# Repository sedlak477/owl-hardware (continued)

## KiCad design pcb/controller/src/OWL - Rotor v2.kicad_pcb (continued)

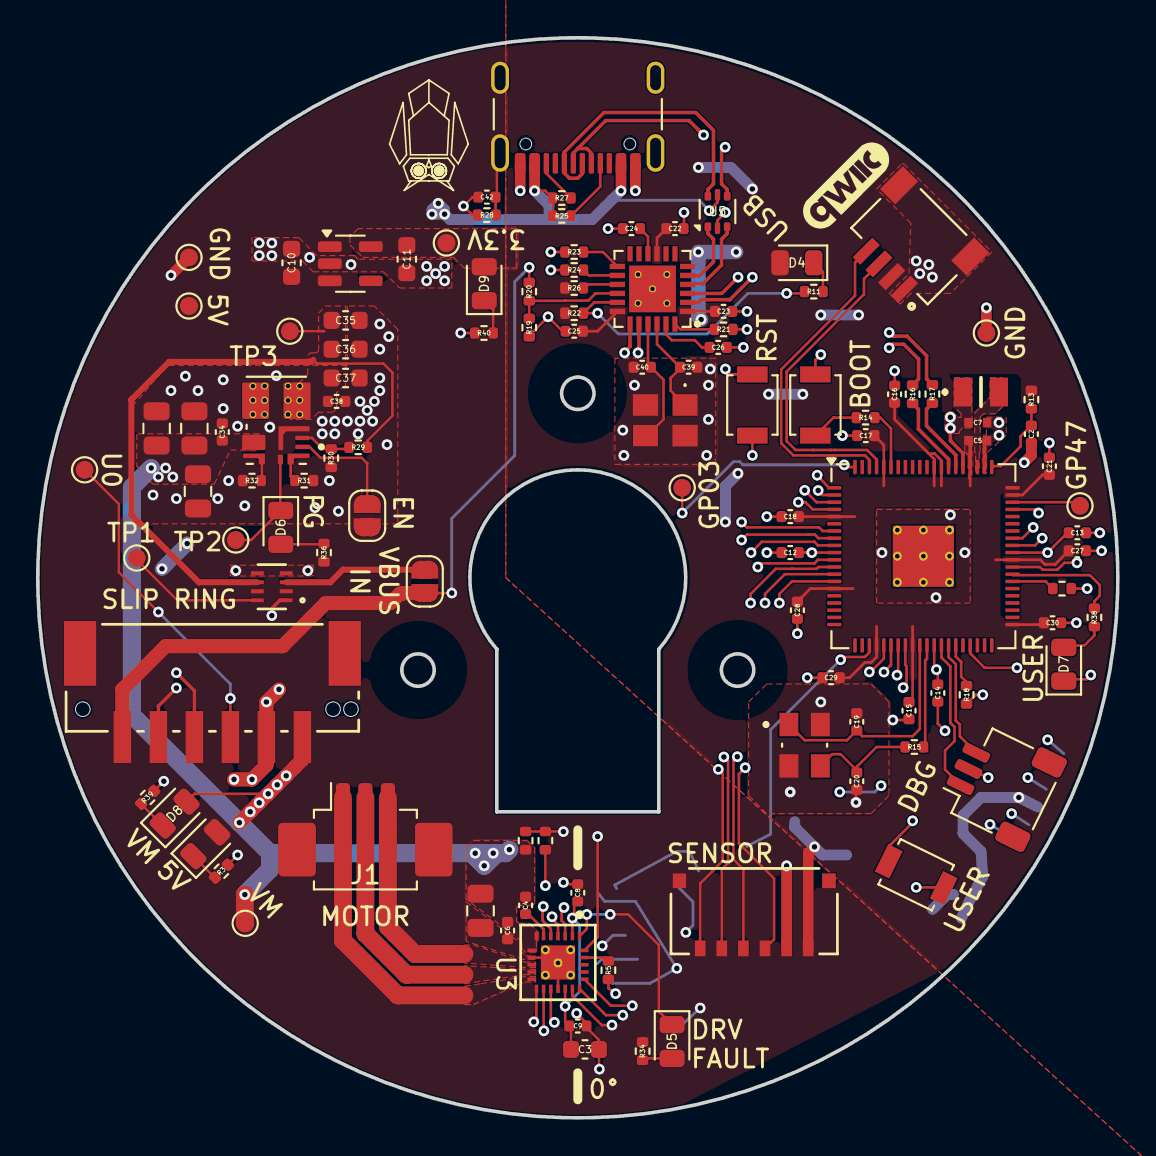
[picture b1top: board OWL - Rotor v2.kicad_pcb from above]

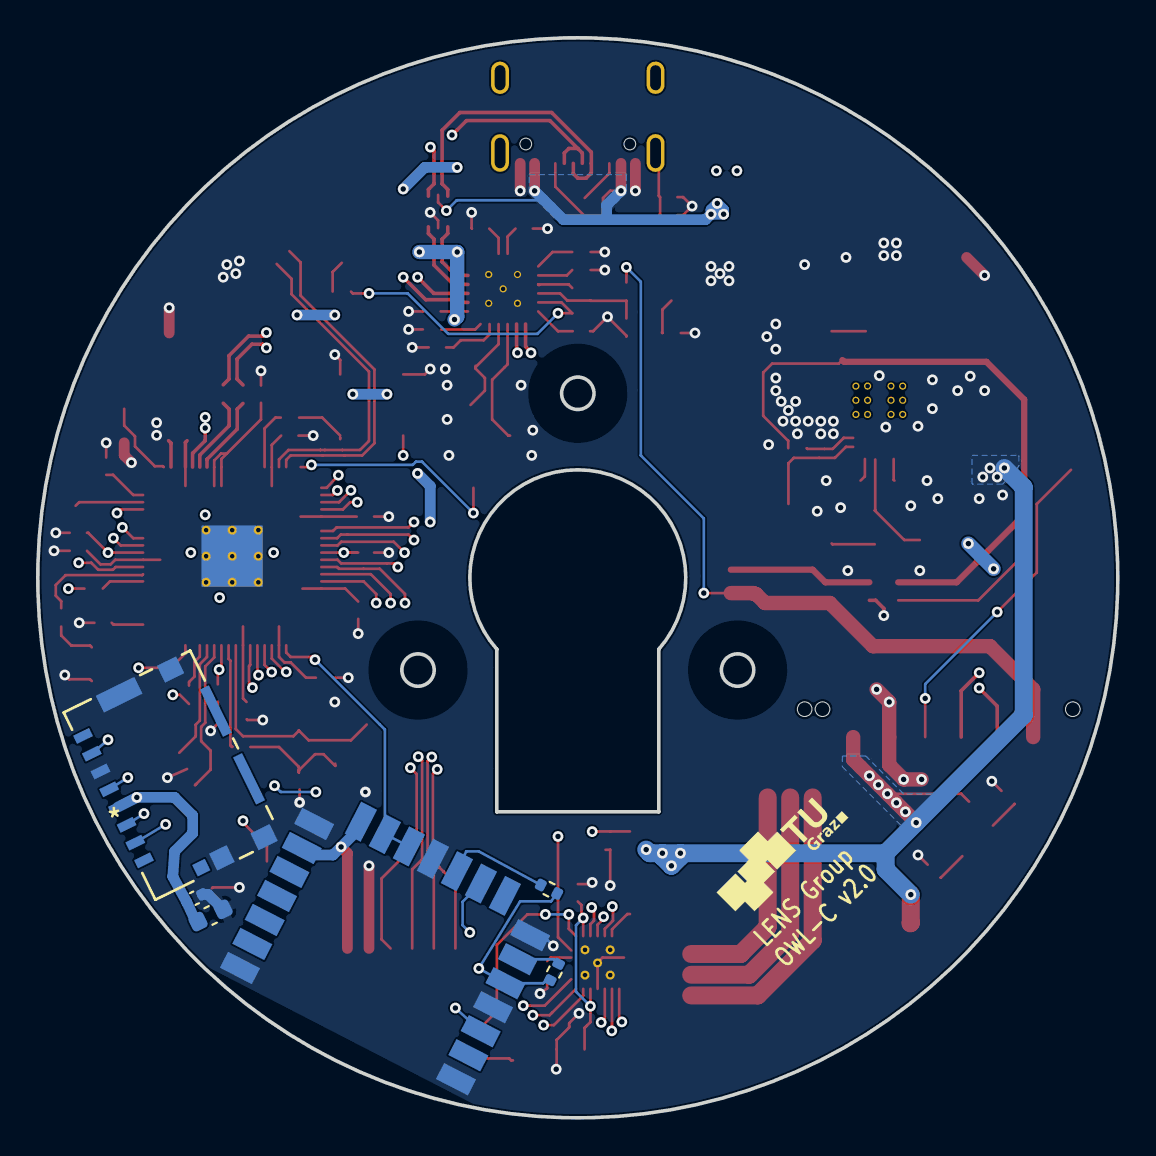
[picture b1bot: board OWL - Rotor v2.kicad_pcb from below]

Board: 4 copper layers, 60.0 x 60.0 mm, 117 parts (6 on the bottom side), 93 nets.

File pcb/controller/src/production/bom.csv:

Designator,Footprint,Quantity,Value,LCSC Part #
C1,0805,1,10u 50V,C28241
"C10, C11, C3, C44",0603,4,10u,
"C12, C13, C15, C16, C17, C18, C21, C23, C25, C26, C27, C28, C29, C30, C38, C43, C8, C9",0402,18,100n,
"C14, C2, C5, C7",0402,4,4.7u,
"C19, C20",0402,2,15p,
"C22, C24",0402,2,1u,
"C31, C32, C33",0805,3,10u 50V,
"C34, C4, C6",0402,3,100n 50V,
"C35, C36, C37",0603,3,22u,
"C39, C40",0402,2,18p,
C42,0402,1,100n 250V,
"D2, D8, D9",0805,3,KT-0805G,
D4,0805,1,KT-0805Y,
"D5, D6",0805,2,KT-0805R,
D7,0805,1,XL-1608UBC-04,
IC1,QFN50P400X400X100-25N,1,USB2422-I_MJ,
J1,Molex_PicoBlade_53261-0371_1x03-1MP_P1.25mm_Horizontal,1,Motor,
J3,USB_C_Receptacle_GCT_USB4105-xx-A_16P_TopMnt_Horizontal,1,USB_C_Receptacle_USB2.0_14P,
J4,CONN_BM06B-PASS-1_JST,1,Slip Ring,
J5,CONN06_781715006_MOL,1,781715006,
J6,JST_SH_SM03B-SRSS-TB_1x03-1MP_P1.00mm_Horizontal,1,SM03B-SRSS-TB,
J8,105162-0001_MOL,1,Micro_SD_Card,C3177046
J9,JST_SM04B-SRSS-TB_LF__SN_,1,SM04B-SRSS-TB_LF__SN_,C160404
L1,AOTAB201610S3R3101T,1,3.3u,
PS1,CONV_TPSM84338RCJR,1,TPSM84338RCJR,
R1,0402,1,470,
R11,0402,1,270,
R13,0402,1,33,
"R14, R15, R18, R34, R36, R41",0402,6,1k,
"R16, R17",0402,2,27,
"R19, R20",0402,2,100k,
"R2, R4",0402,2,10k,
R21,0402,1,12k,
"R22, R23, R24, R26, R5",0402,5,47k,
"R25, R27",0402,2,22k,
R28,0402,1,330,
R29,0402,1,110k,
R3,0402,1,510,
R30,0402,1,15k,
R31,0402,1,0,
R32,0402,1,18k,
R38,0402,1,360,
R39,0402,1,4.7k,
R40,0402,1,150,
R6,0402,1,1.43k,
SW1,SW_SPST_B3U-1000P,1,BOOTSEL,
SW2,SW_SPST_B3U-1000P,1,RESET,
SW3,SW_SPST_B3U-1000P,1,USER,
TP1,TestPoint_Pad_D1.0mm,1,STATUS,
TP10,TestPoint_Pad_D1.0mm,1,GP03,
"TP12, TP7",TestPoint_Pad_D1.0mm,2,GND,
TP2,TestPoint_Pad_D1.0mm,1,REG PG,
TP3,TestPoint_Pad_D1.0mm,1,REG 5V,
TP4,TestPoint_Pad_D1.0mm,1,3.3V,
TP5,TestPoint_Pad_D1.0mm,1,GP47,
TP6,TestPoint_Pad_D1.0mm,1,5V,
TP8,TestPoint_Pad_D1.0mm,1,U0,
TP9,TestPoint_Pad_D1.0mm,1,VMotor,
U1,SOT-23-5,1,AP2112K-3.3,C23380830
U2,SOT-5X3_DRL_TEX,1,LM66200DRLR,
U3,RRW0024-MFG,1,PDRV8311HRRWR,
U4,QFN-80-1EP_10x10mm_P0.4mm_EP3.4x3.4mm_ThermalVias,1,RP2354B,
U5,SOT-666,1,USBLC6-2P6,
U6,rpi_rmc20452t,1,<value>,
Y1,XTAL_ABM8-272-T3,1,ABM8-272-T3,
Y2,7M24000MAAJT,1,7M-24.000MAAJ-T,

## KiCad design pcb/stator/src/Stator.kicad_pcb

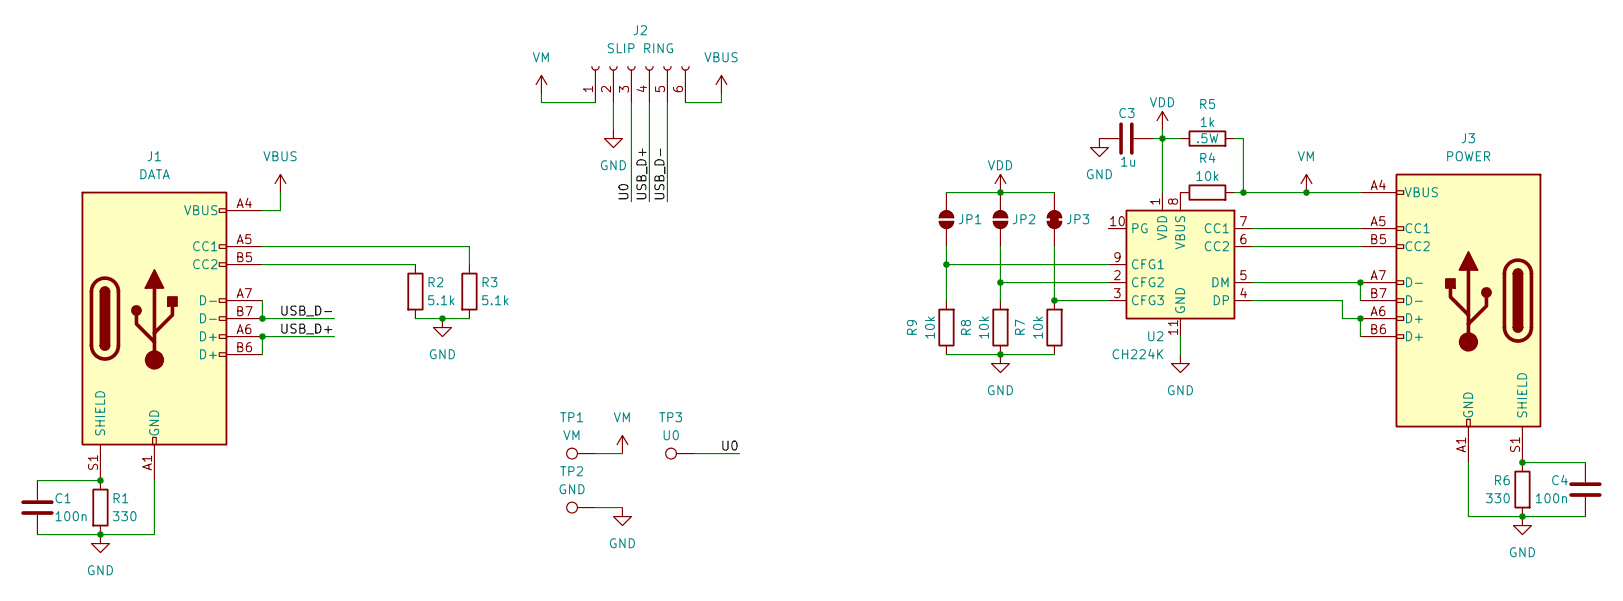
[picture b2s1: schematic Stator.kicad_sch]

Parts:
C1, C4: 100n; C_0402_1005Metric; MPN 0402F104M500NT; LCSC C1581
C3: 1u; C_0402_1005Metric; MPN CL05A105KA5NQNC; LCSC C52923
J1: DATA; USB_C_Receptacle_GCT_USB4110; MPN USB4110-GF-A; LCSC C5143397
J2: SLIP RING; CONN_BM06B-PASS-1_JST; MPN BM06B-PASS-TFT(LF)(SN); LCSC C265376
J3: POWER; USB_C_Receptacle_GCT_USB4110; MPN USB4110-GF-A; LCSC C5143397
JP1: C1; SolderJumper-2_P1.3mm_Open_RoundedPad1.0x1.5mm
JP2: C2; SolderJumper-2_P1.3mm_Open_RoundedPad1.0x1.5mm
JP3: C3; SolderJumper-2_P1.3mm_Bridged_RoundedPad1.0x1.5mm
R1, R6: 330; R_0402_1005Metric; MPN 0402WGF3300TCE; LCSC C25104
R2, R3: 5.1k; R_0402_1005Metric; MPN 0402WGF5101TCE; LCSC C25905
R4, R7, R8, R9: 10k; R_0402_1005Metric; MPN 0402WGF1002TCE; LCSC C25744
R5: 1k; R_0805_2012Metric; MPN AS05W2J0102T5E; LCSC C560481
TP1: VM; TestPoint_Pad_2.0x2.0mm
TP2: GND; TestPoint_Pad_2.0x2.0mm
TP3: U0; TestPoint_Pad_2.0x2.0mm
U2: CH224K; SSOP-10-1EP_3.9x4.9mm_P1mm_EP2.1x3.3mm; MPN CH224K; LCSC C970725

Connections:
/U0: J2.3, TP3.1
/USB_D+: J1.A6 (D+), J1.B6 (D+), J2.4
/USB_D-: J1.A7 (D-), J1.B7 (D-), J2.5
GND: C1.2, C3.2, C4.2, J1.A1 (GND), J1.A12 (GND), J1.B1 (GND), J1.B12 (GND), J2.2, J3.A1 (GND), J3.A12 (GND), J3.B1 (GND), J3.B12 (GND), R1.2, R2.2, R3.2, R6.2, R7.1, R8.1, R9.1, TP2.1, U2.11 (GND)
unnamed: J1.A5 (CC1), R3.1
unnamed: J1.B5 (CC2), R2.1
unnamed: C1.1, J1.S1 (SHIELD), R1.1
unnamed: J3.A5 (CC1), U2.7 (CC1)
unnamed: J3.B5 (CC2), U2.6 (CC2)
unnamed: C4.1, J3.S1 (SHIELD), R6.1
unnamed: JP1.1 (A), R9.2, U2.9 (CFG1)
unnamed: JP2.1 (A), R8.2, U2.2 (CFG2)
unnamed: JP3.1 (A), R7.2, U2.3 (CFG3)
unnamed: J3.A7 (D-), J3.B7 (D-), U2.5 (DM)
unnamed: J3.A6 (D+), J3.B6 (D+), U2.4 (DP)
unnamed: R4.1, U2.8 (VBUS)
VBUS: J1.A4 (VBUS), J1.A9 (VBUS), J1.B4 (VBUS), J1.B9 (VBUS), J2.6
VDD: C3.1, JP1.2 (B), JP2.2 (B), JP3.2 (B), R5.1, U2.1 (VDD)
VM: J2.1, J3.A4 (VBUS), J3.A9 (VBUS), J3.B4 (VBUS), J3.B9 (VBUS), R4.2, R5.2, TP1.1

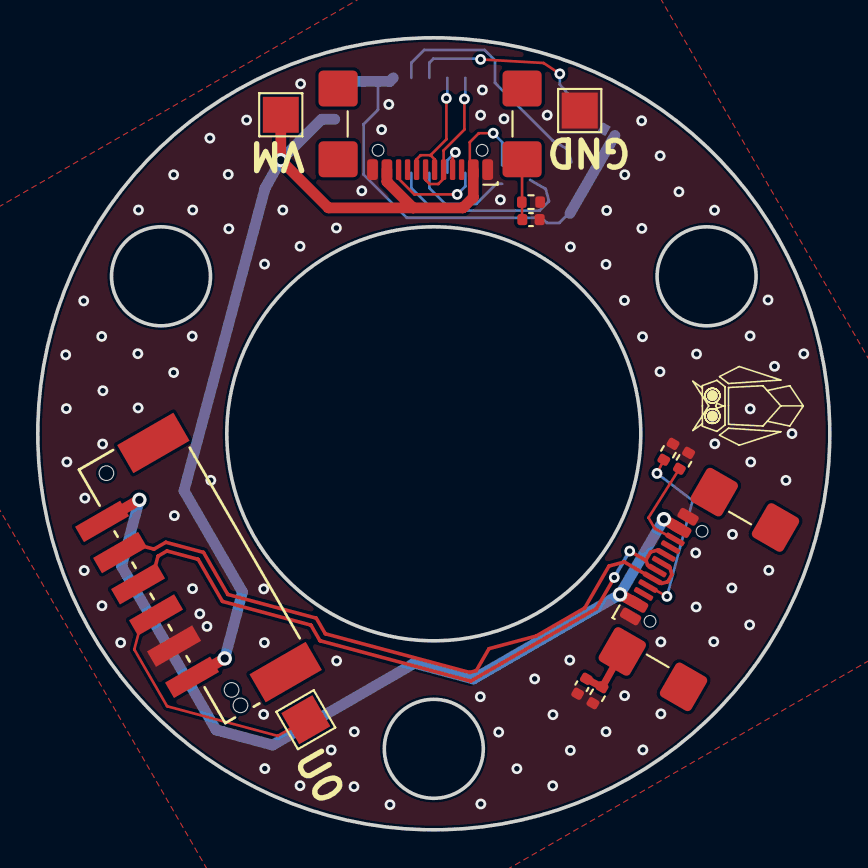
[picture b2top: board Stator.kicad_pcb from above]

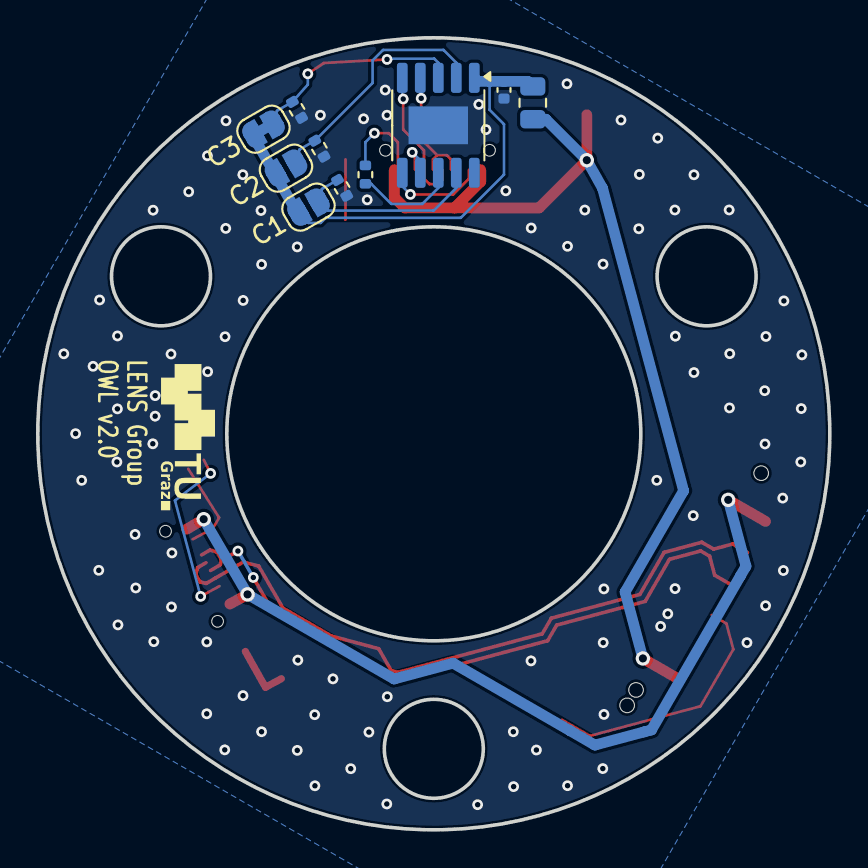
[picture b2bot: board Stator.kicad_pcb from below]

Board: 2 copper layers, 44.0 x 44.0 mm, 22 parts (10 on the bottom side), 19 nets.

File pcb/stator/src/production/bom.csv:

Designator,Footprint,Quantity,Value,LCSC Part #
"C1, C4",0402,2,100n,
C3,0402,1,1u,
J1,USB_C_Receptacle_GCT_USB4110,1,DATA,
J2,CONN_BM06B-PASS-1_JST,1,SLIP RING,C265376
J3,USB_C_Receptacle_GCT_USB4110,1,POWER,
"R1, R6",0402,2,330,
"R2, R3",0402,2,5.1k,
"R4, R7, R8, R9",0402,4,10k,
R5,0805,1,1k,
TP1,TestPoint_Pad_2.0x2.0mm,1,VM,
TP2,TestPoint_Pad_2.0x2.0mm,1,GND,
TP3,TestPoint_Pad_2.0x2.0mm,1,U0,
U2,SSOP-10-1EP_3.9x4.9mm_P1mm_EP2.1x3.3mm,1,CH224K,C970725

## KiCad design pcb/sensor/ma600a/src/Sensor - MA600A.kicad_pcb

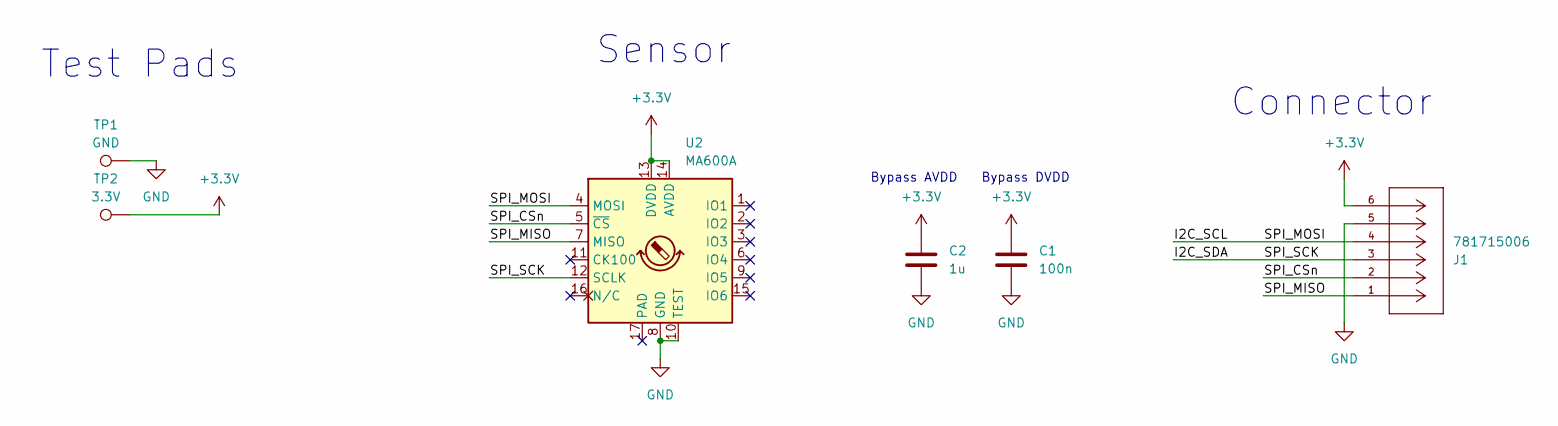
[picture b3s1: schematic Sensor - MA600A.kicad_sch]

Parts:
C1: 100n; C_0603_1608Metric; MPN CC0603KRX7R9BB104; LCSC C14663
C2: 1u; C_0603_1608Metric; MPN CL10A105KB8NNNC; LCSC C15849
J1: 781715006; CONN06_781715006_MOL; MPN 781715006; LCSC C107412
TP1: GND; TestPoint_Pad_D1.5mm
TP2: 3.3V; TestPoint_Pad_D1.5mm
U2: MA600A; QFN-16-1EP_3x3mm_P0.5mm_EP1.75x1.75mm; MPN MA600AGQE-0000-Z; LCSC C49240579

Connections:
+3.3V: C1.1, C2.1, J1.6, TP2.1, U2.13 (DVDD), U2.14 (AVDD)
/I2C_SCL: J1.4, U2.4 (MOSI)
/I2C_SDA: J1.3, U2.12 (SCLK)
/SPI_CSn: J1.2, U2.5 (~CS)
/SPI_MISO: J1.1, U2.7 (MISO)
GND: C1.2, C2.2, J1.5, TP1.1, U2.8 (GND), U2.10 (TEST)

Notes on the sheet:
Test Pads
Bypass DVDD
Connector
Bypass AVDD
Sensor

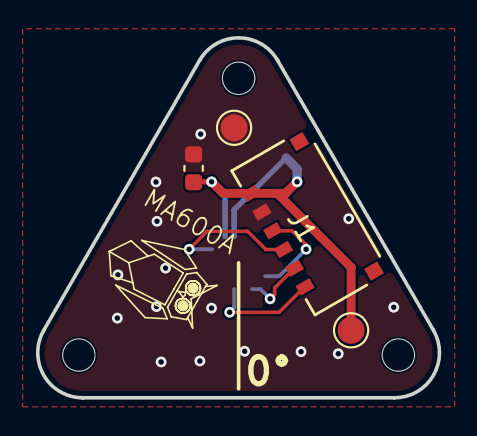
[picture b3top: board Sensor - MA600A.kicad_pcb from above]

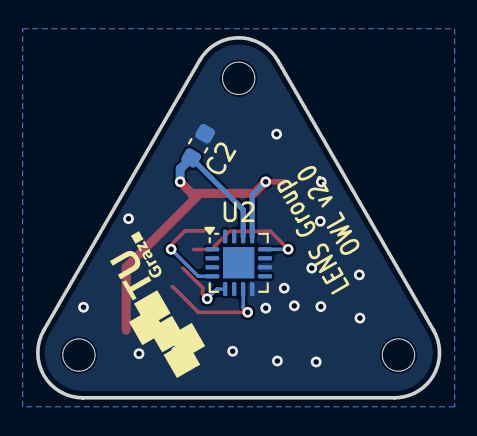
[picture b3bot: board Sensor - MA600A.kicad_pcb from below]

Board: 2 copper layers, 22.3 x 20.0 mm, 9 parts (2 on the bottom side), 6 nets.

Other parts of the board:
H1, H2, H3: MountingHole_1.8mm_M1.6

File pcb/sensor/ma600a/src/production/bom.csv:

Designator,Footprint,Quantity,Value,LCSC Part #
C1,0603,1,100n,
C2,0603,1,1u,
J1,CONN06_781715006_MOL,1,781715006,
TP1,TestPoint_Pad_D1.5mm,1,GND,
TP2,TestPoint_Pad_D1.5mm,1,3.3V,
U2,QFN-16-1EP_3x3mm_P0.5mm_EP1.75x1.75mm,1,MA600A,
